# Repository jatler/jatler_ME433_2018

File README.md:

Johnny Atler
April 6, 2018

ME 433: Advanced Mechatronics Course Repository

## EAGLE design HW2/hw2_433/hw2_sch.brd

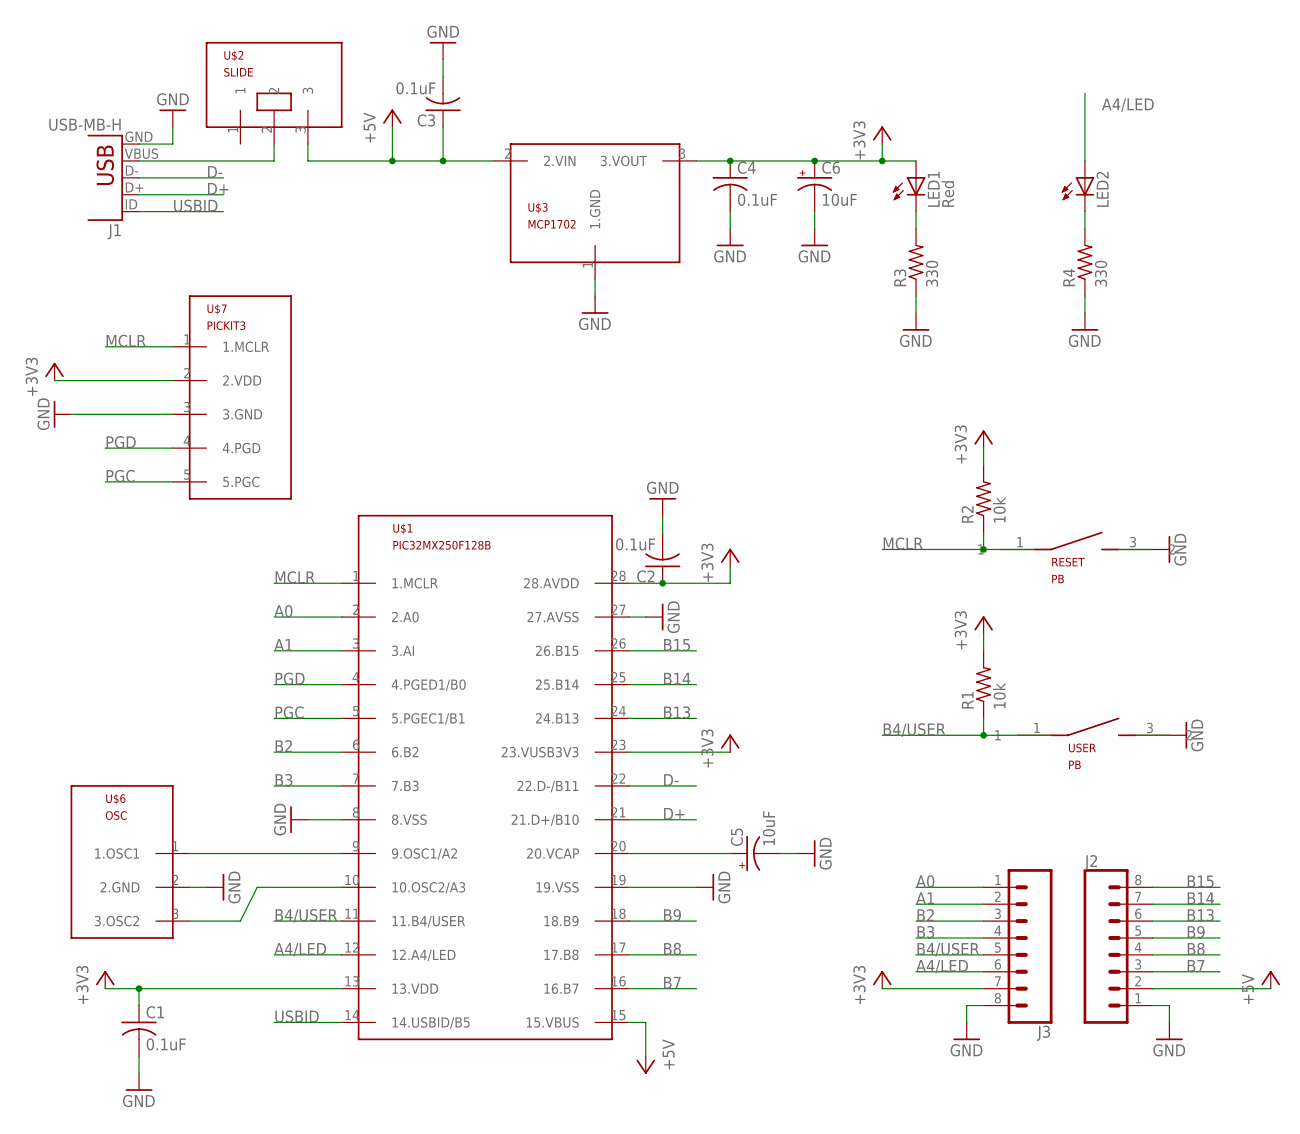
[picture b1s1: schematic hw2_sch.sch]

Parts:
C1, C2, C3, C4: 0.1uF; C025-025X050
C5, C6: 10uF; B45181B
J1: USB-MB-H
J2, J3: CONN_08"; 1X08
LED1: Red; LED3MM
LED2: LED3MM
R1, R2: 10k; 0207/10
R3, R4: 330; 0207/10
RESET: PB
U$1: PIC32MX250F128B; DIL28-3
U$2: SLIDE
U$3: MCP1702; TO92
U$6: OSC
U$7: PICKIT3; 1X05
USER: PB

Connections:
+3V3: C1.1, C2.1, C4.1, C6.+, J3.7, LED1.A, R1.2, R2.2, U$1.13 (13.VDD), U$1.23 (23.VUSB3V3), U$1.28 (28.AVDD), U$3.3 (3.VOUT), U$7.2 (2.VDD)
+5V: C3.1, J2.2, U$1.15 (15.VBUS), U$2.3, U$3.2 (2.VIN)
A0: J3.1, U$1.2 (2.A0)
A1: J3.2, U$1.3 (3.AI)
A4/LED: J3.6, LED2.A, U$1.12 (12.A4/LED)
B2: J3.3, U$1.6 (6.B2)
B3: J3.4, U$1.7 (7.B3)
B4/USER: J3.5, R1.1, U$1.11 (11.B4/USER), USER.1
B7: J2.3, U$1.16 (16.B7)
B8: J2.4, U$1.17 (17.B8)
B9: J2.5, U$1.18 (18.B9)
B13: J2.6, U$1.24 (24.B13)
B14: J2.7, U$1.25 (25.B14)
B15: J2.8, U$1.26 (26.B15)
D+: J1.D+, U$1.21 (21.D+/B10)
D-: J1.D-, U$1.22 (22.D-/B11)
GND: C1.2, C2.2, C3.2, C4.2, C5.-, C6.-, J1.GND, J2.1, J3.8, R3.1, R4.1, RESET.3 (2), U$1.8 (8.VSS), U$1.19 (19.VSS), U$1.27 (27.AVSS), U$3.1 (1.GND), U$6.2 (2.GND), U$7.3 (3.GND), USER.3 (2)
MCLR: R2.1, RESET.1, U$1.1 (1.MCLR), U$7.1 (1.MCLR)
unnamed: J1.VBUS, U$2.2
unnamed: U$1.9 (9.OSC1/A2), U$6.1 (1.OSC1)
unnamed: LED1.K (C), R3.2
unnamed: U$1.10 (10.OSC2/A3), U$6.3 (3.OSC2)
unnamed: C5.+, U$1.20 (20.VCAP)
unnamed: LED2.K (C), R4.2
PGC: U$1.5 (5.PGEC1/B1), U$7.5 (5.PGC)
PGD: U$1.4 (4.PGED1/B0), U$7.4 (4.PGD)
USBID: J1.ID, U$1.14 (14.USBID/B5)

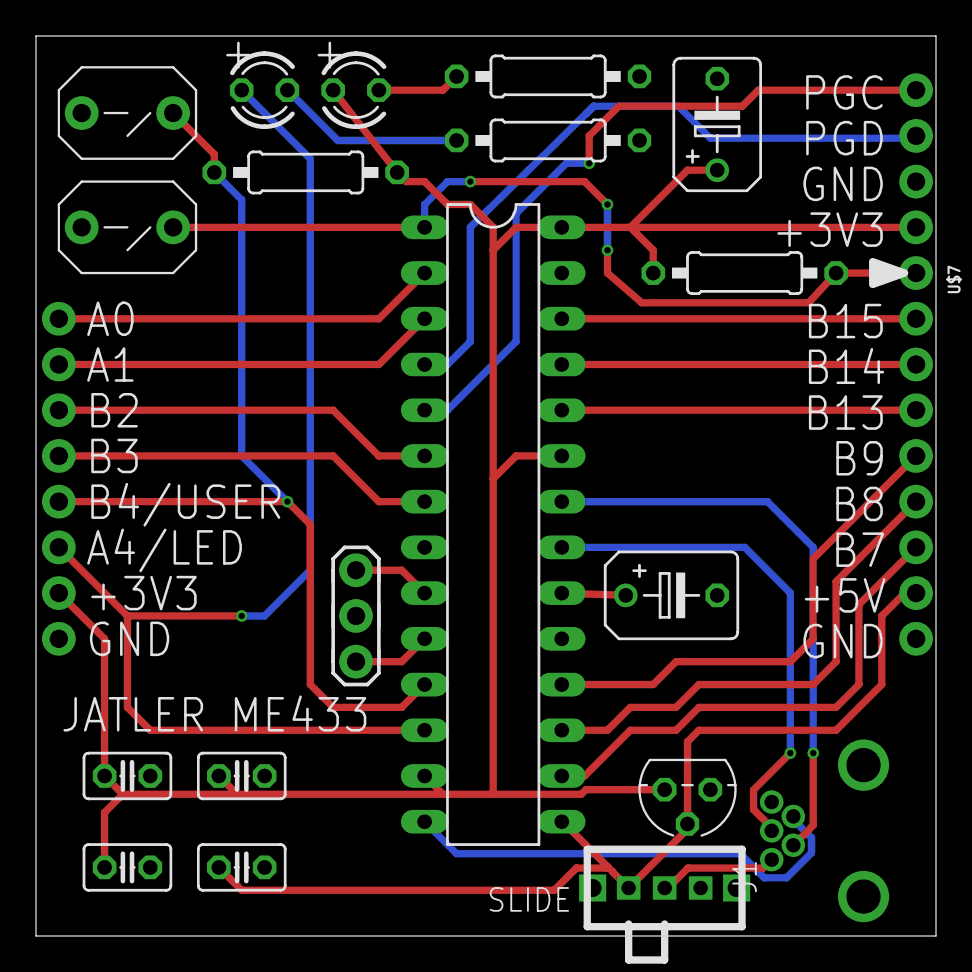
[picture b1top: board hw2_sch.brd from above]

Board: 2 copper layers, 50.0 x 50.0 mm, 22 parts (0 on the bottom side), 27 nets.

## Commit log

2018-04-06 Hello world!
2018-04-09 Circuit diagram
2018-04-10 Oscilloscope readouts and completed breadboard
2018-04-10 Initial code with completed pragmas
2018-04-10 Initialized pushbutton and LED pins
2018-04-10 Code with 1ms square wave and pushbutton
2018-04-11 Created library
2018-04-12 Completed schematic and library updates
2018-04-17 Updated board
2018-04-17 Gerber files created
2018-04-17 Added logo
2018-04-17 Updated gerber
2018-04-19 Updated SPI code
2018-04-24 Updated SPI and I2C code
2018-04-24 Completed HW5 I2C code
2018-04-24 MCP23008 Circuit Diagram
2018-04-26 Fixed SPI code and added results
2018-04-27 SPI Circuit Diagram
2018-05-07 HW6 LCD updates
2018-05-15 HW7 IMU Updates
2018-05-15 Revert "HW7 IMU Updates"
    This reverts commit 517c2f05c76f5cef1d6cc05cec3b9fb46eb1f350.
2018-05-15 Revert "Revert "HW7 IMU Updates""
    This reverts commit 866fe9b3f45daeaeb5cca7e7bac48aa1355f0461.
2018-05-15 HW8 Harmony configuration
2018-05-22 HW9 CDC updates
2018-05-23 HW10 progress
2018-05-23 HW12 completed
2018-05-24 HW13 android studio
2018-05-28 HW14 AndroidUSB updates
2018-05-31 HW10 completed
2018-05-31 HW11 completed
2018-05-31 HW12 video
2018-06-06 Android Image Processing and TechCup updates
2018-06-14 HW 18 TechCup completed
2018-06-14 Robot design images
2018-06-14 HW 13 demo video
